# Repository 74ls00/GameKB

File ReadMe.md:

[Форум проекта](https://forum.geekboards.ru/viewtopic.php?t=13140)

------------------------------------------------------------------------------------

Easy AVR USB Keyboard Firmware Keymapper 
прошивка и графический конфигурфтор клавиш.

https://github.com/74ls00/GameKB_fw

Полная версия клавиатуры.

------------------------------------------------------------------------------------

tmk_keyboard \keyboard\korbord прошивка контролера 6KRO, готов только нумпад.

https://github.com/74ls00/GameKB_tmk

------------------------------------------------------------------------------------

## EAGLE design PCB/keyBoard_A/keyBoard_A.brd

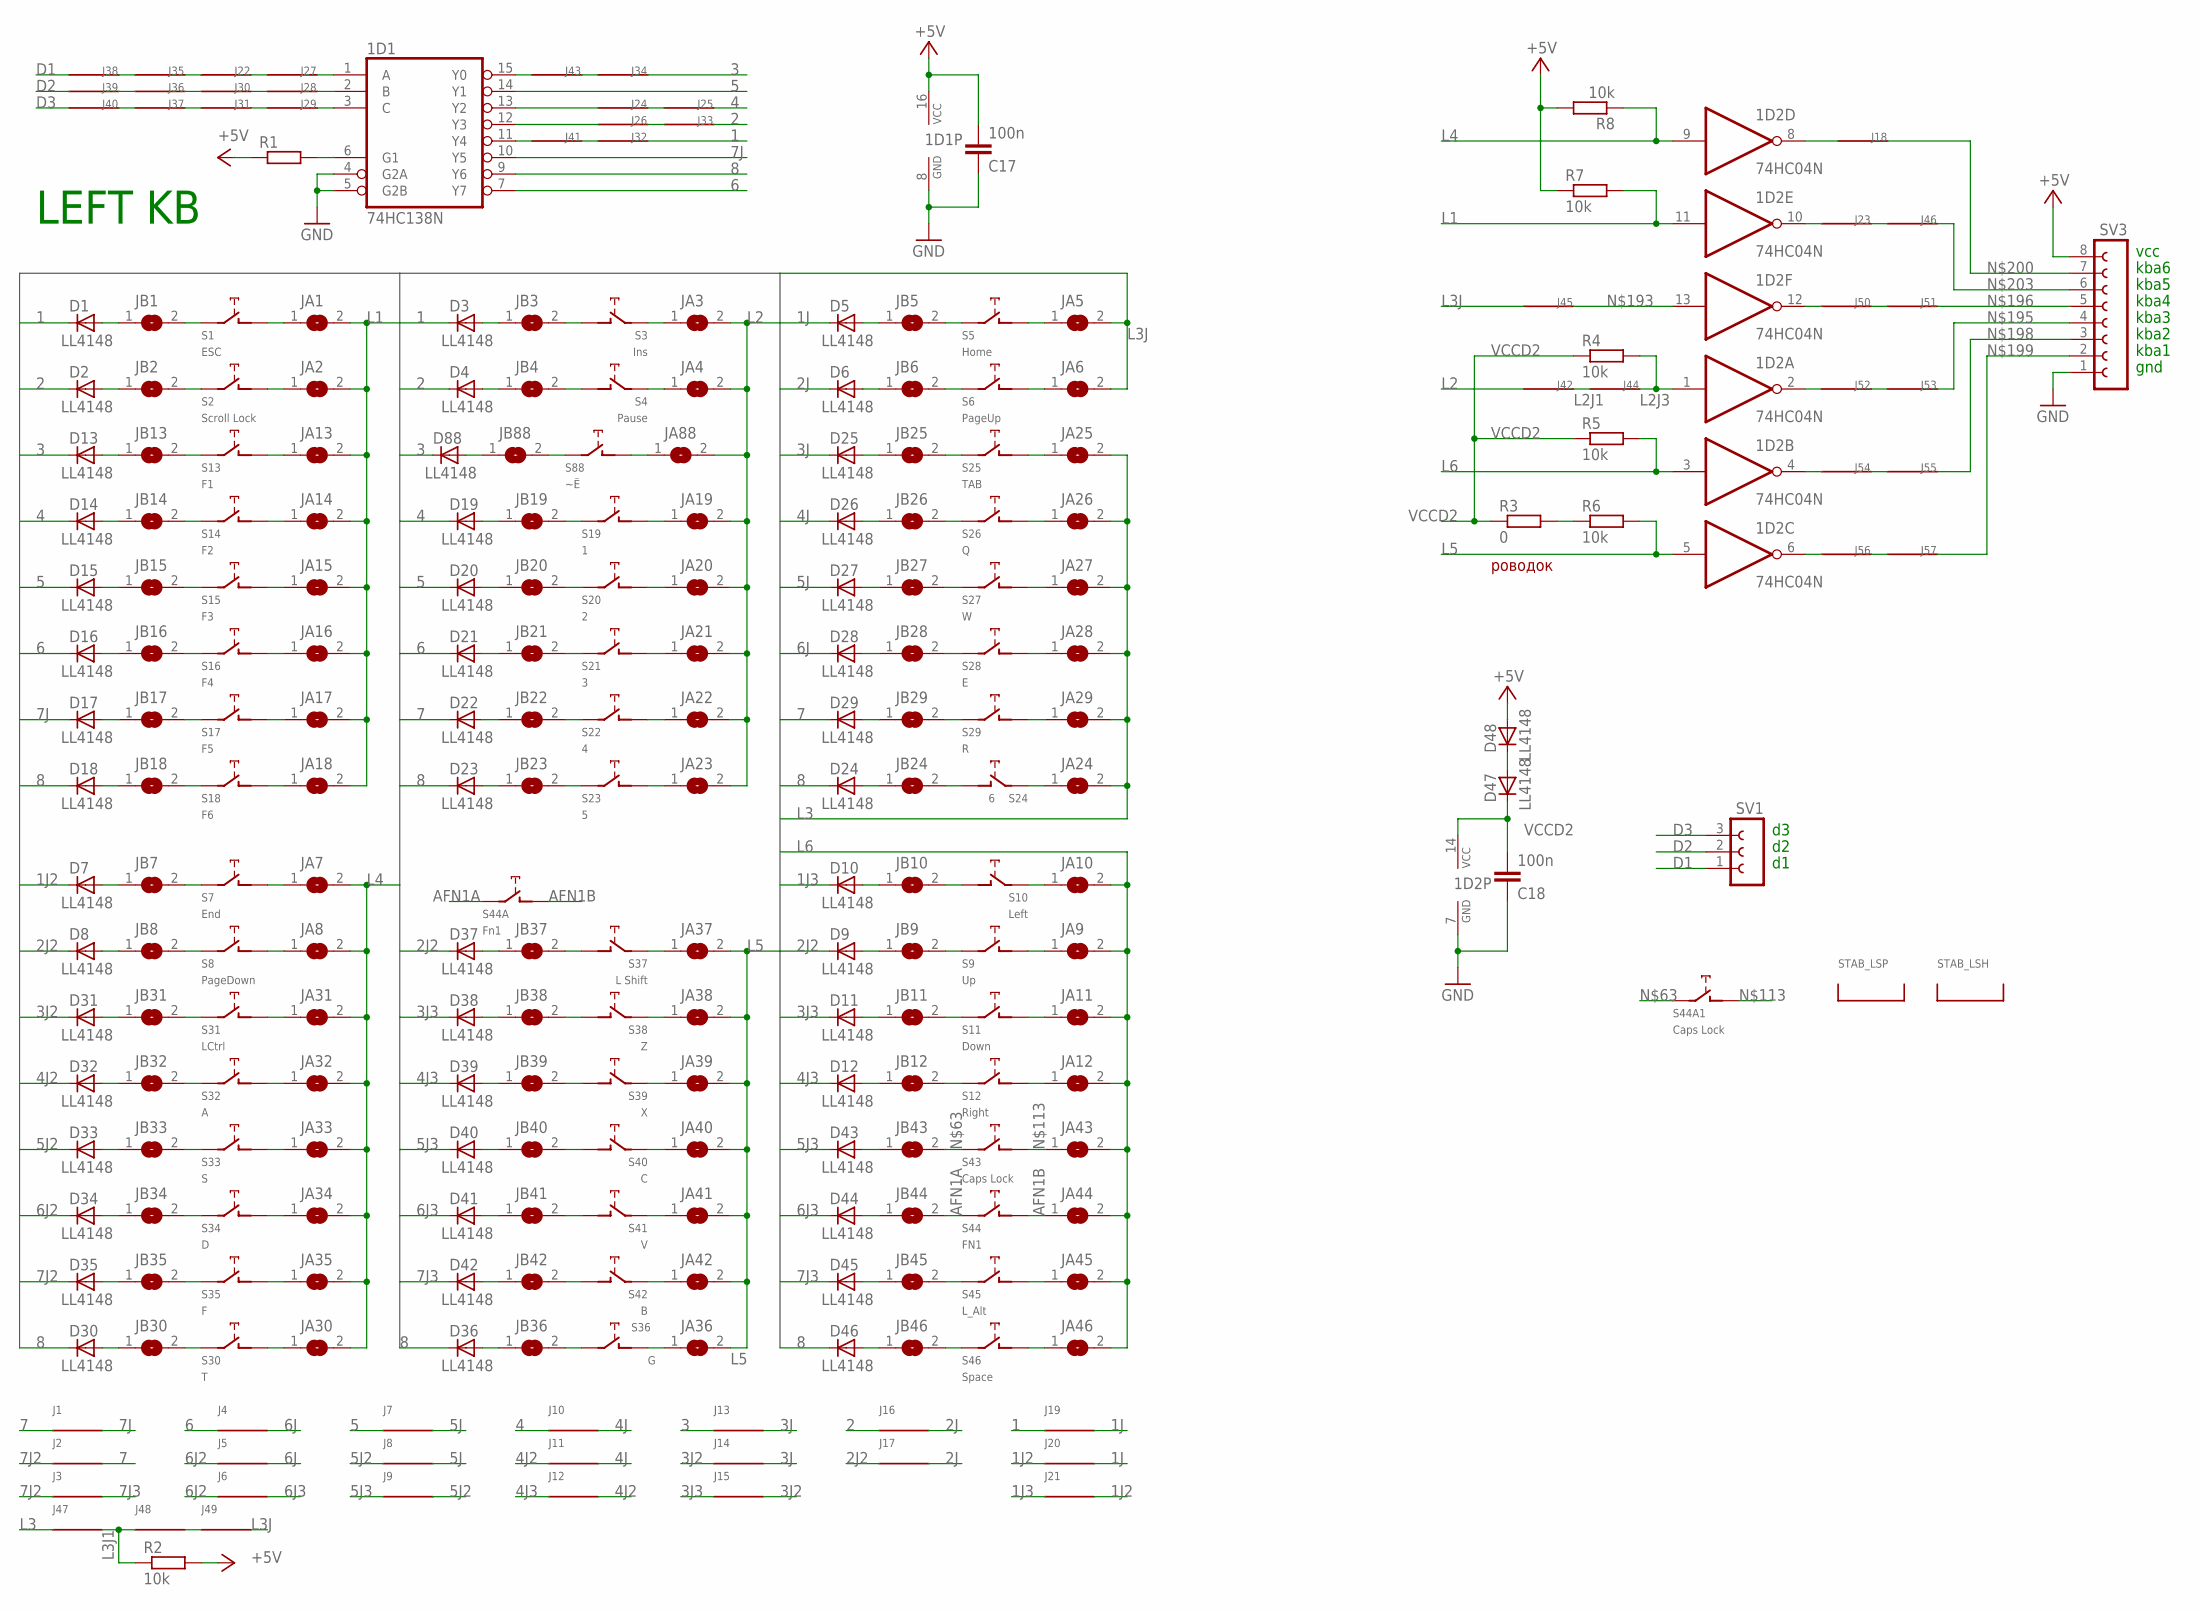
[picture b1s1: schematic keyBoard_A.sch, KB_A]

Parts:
1D1: 74HC138N; DIL16
1D2: 74HC04N; DIL14
C17, C18: 100n; C0805
D1, D2, D3, D4, D5, D6, D7, D8, D9, D10, D11, D12, D13, D14, D15, D16, D17, D18, D19, D20, D21, D22, D23, D24, D25, D26, D27, D28, D29, D30, D31, D32, D33, D34, D35, D36, D37, D38, D39, D40, D41, D42, D43, D44, D45, D46, D47, D48, D88: LL4148; SOD80C
J1, J2, J3, J4, J5, J6, J7, J8, J9, J10, J11, J12, J13, J14, J15, J16, J17, J18, J19, J20, J21, J22, J23, J24, J25, J26, J27, J28, J29, J30, J31, J32, J33, J34, J35, J36, J37, J38, J39, J40, J41, J42, J43, J44, J45, J46, J47, J48, J49, J50, J51, J52, J53, J54, J55, J56, J57: J; R1206W
JA1, JA2, JA3, JA4, JA5, JA6, JA7, JA8, JA9, JA10, JA11, JA12, JA13, JA14, JA15, JA16, JA17, JA18, JA19, JA20, JA21, JA22, JA23, JA24, JA25, JA26, JA27, JA28, JA29, JA30, JA31, JA32, JA33, JA34, JA35, JA36, JA37, JA38, JA39, JA40, JA41, JA42, JA43, JA44, JA45, JA46, JA88: SJ
JB1, JB3, JB4, JB6, JB7, JB8, JB9, JB10, JB11, JB12, JB13, JB16, JB17, JB18, JB19, JB20, JB21, JB22, JB23, JB24, JB25, JB26, JB27, JB28, JB29, JB30, JB31, JB32, JB33, JB34, JB35, JB36, JB37, JB38, JB39, JB40, JB41, JB42, JB43, JB44, JB45, JB46, JB88: SJ
JB2, JB5, JB14, JB15: SJ; SJ@1
R1: R-EU_R1206W; R1206W
R2, R5, R6, R7: 10k; R1206W
R3: 0; R1206W
R4, R8: 10k; R0805
S1: ESC; CHERRY-MX-4P
S2: Scroll Lock; CHERRY-MX-4P
S3: Ins; CHERRY-MX-4P
S4: Pause; CHERRY-MX-4P
S5: Home; CHERRY-MX-4P
S6: PageUp; CHERRY-MX-4P
S7: End; CHERRY-MX-4P
S8: PageDown; CHERRY-MX-4P
S9: Up; CHERRY-MX-4P
S10: Left; CHERRY-MX-4P
S11: Down; CHERRY-MX-4P
S12: Right; CHERRY-MX-4P
S13: F1; CHERRY-MX-4P
S14: F2; CHERRY-MX-4P
S15: F3; CHERRY-MX-4P
S16: F4; CHERRY-MX-4P
S17: F5; CHERRY-MX-4P
S18: F6; CHERRY-MX-4P
S19: 1; CHERRY-MX-4P
S20: 2; CHERRY-MX-4P
S21: 3; CHERRY-MX-4P
S22: 4; CHERRY-MX-4P
S23: 5; CHERRY-MX-4P
S24: 6; CHERRY-MX-4P
S25: TAB; CHERRY-MX-4P
S26: Q; CHERRY-MX-4P
S27: W; CHERRY-MX-4P
S28: E; CHERRY-MX-4P
S29: R; CHERRY-MX-4P
S30: T; CHERRY-MX-4P
S31: LCtrl; CHERRY-MX-4P
S32: A; CHERRY-MX-4P
S33: S; CHERRY-MX-4P
S34: D; CHERRY-MX-4P
S35: F; CHERRY-MX-4P
S36: G; CHERRY-MX-4P
S37: L Shift; CHERRY-MX-4P
S38: Z; CHERRY-MX-4P
S39: X; CHERRY-MX-4P
S40: C; CHERRY-MX-4P
S41: V; CHERRY-MX-4P
S42: B; CHERRY-MX-4P
S43: Caps Lock; CHERRY-MX-4P
S44: FN1; CHERRY-MX-4P
S44A: Fn1; CHERRY-MX
S44A1: Caps Lock; CHERRY-MX
S45: L_Alt; CHERRY-MX-4P
S46: Space; CHERRY-MX-4P
S88: ~Ё; CHERRY-MX-4P
STAB_LSH: STAB; ZEALIOS-PCB_2U
STAB_LSP: STAB; ZEALIOS-PCB_2U
SV1: FE03-1
SV3: FE08-1; FE08

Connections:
1: D1.C, D3.C, J19.2, J32.1
1J: D5.C, J19.1, J20.1
1J2: D7.C, J20.2, J21.1
1J3: D10.C, J21.2
2: D2.C, D4.C, J16.2, J33.1
2J: D6.C, J16.1, J17.1
2J2: D8.C, D9.C, D37.C, J17.2
3: D13.C, D88.C, J13.2, J34.1
3J: D25.C, J13.1, J14.1
3J2: D31.C, J14.2, J15.1
3J3: D11.C, D38.C, J15.2
4: D14.C, D19.C, J10.2, J25.1
4J: D26.C, J10.1, J11.1
4J2: D32.C, J11.2, J12.1
4J3: D12.C, D39.C, J12.2
5: 1D1.14 (Y1), D15.C, D20.C, J7.2
5J: D27.C, J7.1, J8.1
5J2: D33.C, J8.2, J9.1
5J3: D40.C, D43.C, J9.2
6: 1D1.7 (Y7), D16.C, D21.C, J4.2
6J: D28.C, J4.1, J5.1
6J2: D34.C, J5.2, J6.2
6J3: D41.C, D44.C, J6.1
7: D22.C, D29.C, J1.2, J2.1
7J: 1D1.10 (Y5), D17.C, J1.1
7J2: D35.C, J2.2, J3.2
7J3: D42.C, D45.C, J3.1
8: 1D1.9 (Y6), D18.C, D23.C, D24.C, D30.C, D36.C, D46.C
+5V: 1D1.16 (VCC), C17.2, D48.A, R1.1, R2.2, R7.1, R8.2, SV3.8
AFN1A: JB44.2, S44.SW1 (PIN-1), S44A.SW1 (PIN-1)
AFN1B: JA44.1, S44.SW2 (PIN-2), S44A.SW2 (PIN-2)
D1: J38.2, SV1.1
D2: J39.2, SV1.2
D3: J40.2, SV1.3
GND: 1D1.4 (G2A), 1D1.5 (G2B), 1D1.8 (GND), 1D2.7 (GND), C17.1, C18.1, SV3.1
L1: 1D2.11 (I), JA1.2, JA2.2, JA13.2, JA14.2, JA15.2, JA16.2, JA17.2, JA18.2, R7.2
L2: J42.2, JA3.2, JA4.2, JA19.2, JA20.2, JA21.2, JA22.2, JA23.2, JA88.2
L2J1: J42.1, J44.2
L2J3: 1D2.1 (I), J44.1, R4.2
L3: J47.2, JA24.2, JA25.2, JA26.2, JA27.2, JA28.2, JA29.2
L3J: J45.2, J49.1, JA5.2, JA6.2
L3J1: J47.1, J48.2, R2.1
L4: 1D2.9 (I), JA7.2, JA8.2, JA30.2, JA31.2, JA32.2, JA33.2, JA34.2, JA35.2, R8.1
L5: 1D2.5 (I), JA36.2, JA37.2, JA38.2, JA39.2, JA40.2, JA41.2, JA42.2, R6.2
L5O: 1D2.6 (O), J56.2
L6: 1D2.3 (I), JA9.2, JA10.2, JA11.2, JA12.2, JA43.2, JA44.2, JA45.2, JA46.2, R5.2
unnamed: D15.A, JB15.1
unnamed: JB4.2, S4.SW2 (PIN-2)
unnamed: D1.A, JB1.1
unnamed: JA4.1, S4.SW1 (PIN-1)
unnamed: JB14.2, S14.SW1 (PIN-1)
unnamed: JB20.2, S20.SW1 (PIN-1)
unnamed: JB32.2, S32.SW1 (PIN-1)
unnamed: JB38.2, S38.SW2 (PIN-2)
unnamed: JB6.2, S6.SW1 (PIN-1)
unnamed: JA6.1, S6.SW2 (PIN-2)
unnamed: JA8.1, S8.SW2 (PIN-2)
unnamed: JB8.2, S8.SW1 (PIN-1)
unnamed: JB10.2, S10.SW2 (PIN-2)
unnamed: JB1.2, S1.SW1 (PIN-1)
unnamed: D2.A, JB2.1
unnamed: JB2.2, S2.SW1 (PIN-1)
unnamed: JA2.1, S2.SW2 (PIN-2)
unnamed: D16.A, JB16.1
unnamed: JB3.2, S3.SW2 (PIN-2)
unnamed: JB5.2, S5.SW1 (PIN-1)
unnamed: JB7.2, S7.SW1 (PIN-1)
unnamed: JB9.2, S9.SW1 (PIN-1)
unnamed: JB11.2, S11.SW1 (PIN-1)
unnamed: D3.A, JB3.1
unnamed: JB12.2, S12.SW1 (PIN-1)
unnamed: D5.A, JB5.1
unnamed: D7.A, JB7.1
unnamed: JA10.1, S10.SW1 (PIN-1)
unnamed: JA1.1, S1.SW2 (PIN-2)
unnamed: D9.A, JB9.1
unnamed: D11.A, JB11.1
unnamed: JA3.1, S3.SW1 (PIN-1)
unnamed: JA5.1, S5.SW2 (PIN-2)
unnamed: JA7.1, S7.SW2 (PIN-2)
unnamed: JA9.1, S9.SW2 (PIN-2)
unnamed: JA11.1, S11.SW2 (PIN-2)
unnamed: JA12.1, S12.SW2 (PIN-2)
unnamed: JA14.1, S14.SW2 (PIN-2)
unnamed: JB13.2, S13.SW1 (PIN-1)
unnamed: JA13.1, S13.SW2 (PIN-2)
unnamed: D14.A, JB14.1
unnamed: JB42.2, S42.SW2 (PIN-2)
unnamed: JA42.1, S42.SW1 (PIN-1)
unnamed: JB27.2, S27.SW1 (PIN-1)
unnamed: JA27.1, S27.SW2 (PIN-2)
unnamed: JB17.2, S17.SW1 (PIN-1)
unnamed: JA17.1, S17.SW2 (PIN-2)
unnamed: D24.A, JB24.1
unnamed: JB24.2, S24.SW2 (PIN-2)
unnamed: JA24.1, S24.SW1 (PIN-1)
unnamed: J22.1, J27.2
unnamed: D4.A, JB4.1
unnamed: D6.A, JB6.1
unnamed: D8.A, JB8.1
unnamed: D10.A, JB10.1
unnamed: D12.A, JB12.1
unnamed: D13.A, JB13.1
unnamed: JB19.2, S19.SW1 (PIN-1)
unnamed: JB25.2, S25.SW1 (PIN-1)
unnamed: 1D2.8 (O), J18.2
unnamed: JB31.2, S31.SW1 (PIN-1)
unnamed: JB37.2, S37.SW2 (PIN-2)
unnamed: JB43.2, S43.SW1 (PIN-1), S44A1.SW1 (PIN-1)
unnamed: JB26.2, S26.SW1 (PIN-1)
unnamed: JB41.2, S41.SW2 (PIN-2)
unnamed: JB18.2, S18.SW1 (PIN-1)
unnamed: 1D1.13 (Y2), J24.2
unnamed: JB30.2, S30.SW1 (PIN-1)
unnamed: JB36.2, S36.SW1 (PIN-1)
unnamed: J24.1, J25.2
unnamed: JB23.2, S23.SW1 (PIN-1)
unnamed: JB29.2, S29.SW1 (PIN-1)
unnamed: JB35.2, S35.SW1 (PIN-1)
unnamed: JA41.1, S41.SW1 (PIN-1)
unnamed: JB16.2, S16.SW1 (PIN-1)
unnamed: JB22.2, S22.SW1 (PIN-1)
unnamed: JB28.2, S28.SW1 (PIN-1)
unnamed: JB34.2, S34.SW1 (PIN-1)
unnamed: JB40.2, S40.SW2 (PIN-2)
unnamed: JB46.2, S46.SW1 (PIN-1)
unnamed: JB15.2, S15.SW1 (PIN-1)
unnamed: JB21.2, S21.SW1 (PIN-1)
unnamed: JB33.2, S33.SW1 (PIN-1)
unnamed: JB39.2, S39.SW2 (PIN-2)
unnamed: JB45.2, S45.SW1 (PIN-1)
unnamed: JA15.1, S15.SW2 (PIN-2)
unnamed: JA18.1, S18.SW2 (PIN-2)
unnamed: JA20.1, S20.SW2 (PIN-2)
unnamed: JA22.1, S22.SW2 (PIN-2)
unnamed: JA23.1, S23.SW2 (PIN-2)
unnamed: JA25.1, S25.SW2 (PIN-2)
unnamed: JA26.1, S26.SW2 (PIN-2)
unnamed: JA28.1, S28.SW2 (PIN-2)
unnamed: JA29.1, S29.SW2 (PIN-2)
unnamed: JA30.1, S30.SW2 (PIN-2)
unnamed: JA31.1, S31.SW2 (PIN-2)
unnamed: JA32.1, S32.SW2 (PIN-2)
unnamed: JA33.1, S33.SW2 (PIN-2)
unnamed: JA34.1, S34.SW2 (PIN-2)
unnamed: JA35.1, S35.SW2 (PIN-2)
unnamed: JA36.1, S36.SW2 (PIN-2)
unnamed: JA38.1, S38.SW1 (PIN-1)
unnamed: JA39.1, S39.SW1 (PIN-1)
unnamed: JA40.1, S40.SW1 (PIN-1)
unnamed: JB88.2, S88.SW1 (PIN-1)
unnamed: JA43.1, S43.SW2 (PIN-2), S44A1.SW2 (PIN-2)
unnamed: JA45.1, S45.SW2 (PIN-2)
unnamed: JA46.1, S46.SW2 (PIN-2)
unnamed: JA19.1, S19.SW2 (PIN-2)
unnamed: JA88.1, S88.SW2 (PIN-2)
unnamed: JA21.1, S21.SW2 (PIN-2)
unnamed: JA16.1, S16.SW2 (PIN-2)
unnamed: D17.A, JB17.1
unnamed: D18.A, JB18.1
unnamed: D19.A, JB19.1
unnamed: D20.A, JB20.1
unnamed: D21.A, JB21.1
unnamed: D22.A, JB22.1
unnamed: D23.A, JB23.1
unnamed: D25.A, JB25.1
unnamed: D26.A, JB26.1
unnamed: D27.A, JB27.1
unnamed: D28.A, JB28.1
unnamed: D29.A, JB29.1
unnamed: D30.A, JB30.1
unnamed: D31.A, JB31.1
unnamed: D32.A, JB32.1
unnamed: D33.A, JB33.1
unnamed: D34.A, JB34.1
unnamed: D35.A, JB35.1
unnamed: D36.A, JB36.1
unnamed: D37.A, JB37.1
unnamed: D38.A, JB38.1
unnamed: D39.A, JB39.1
unnamed: D40.A, JB40.1
unnamed: D41.A, JB41.1
unnamed: D42.A, JB42.1
unnamed: D43.A, JB43.1
unnamed: D44.A, JB44.1
unnamed: D45.A, JB45.1
unnamed: D46.A, JB46.1
unnamed: D88.A, JB88.1
unnamed: 1D1.15 (Y0), J43.2
unnamed: 1D1.1 (A), J27.1
unnamed: 1D1.2 (B), J28.1
unnamed: 1D1.3 (C), J29.1
unnamed: J28.2, J30.1
unnamed: J29.2, J31.1
unnamed: J26.1, J33.2
unnamed: J35.2, J38.1
unnamed: J36.2, J39.1
unnamed: J37.2, J40.1
unnamed: J31.2, J37.1
unnamed: J30.2, J36.1
unnamed: J22.2, J35.1
unnamed: J32.2, J41.1
unnamed: 1D1.11 (Y4), J41.2
unnamed: 1D1.12 (Y3), J26.2
unnamed: J34.2, J43.1
unnamed: D47.A, D48.C
unnamed: 1D2.13 (I), J45.1
unnamed: J53.1, SV3.4
unnamed: J51.1, SV3.5
unnamed: 1D2.10 (O), J23.2
unnamed: J55.1, SV3.3
unnamed: J57.1, SV3.2
unnamed: J18.1, SV3.7
unnamed: J46.1, SV3.6
unnamed: J48.1, J49.2
unnamed: J23.1, J46.2
unnamed: 1D2.12 (O), J50.2
unnamed: J50.1, J51.2
unnamed: 1D2.2 (O), J52.2
unnamed: J52.1, J53.2
unnamed: 1D2.4 (O), J54.2
unnamed: JA37.1, S37.SW1 (PIN-1)
unnamed: J54.1, J55.2
unnamed: J56.1, J57.2
unnamed: R3.2, R6.1
unnamed: 1D1.6 (G1), R1.2
VCCD2: 1D2.14 (VCC), C18.2, D47.C, R3.1, R4.1, R5.1

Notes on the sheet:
vcc
gnd
LEFT KB
kba1
kba2
kba3
kba4
kba5
kba6
роводок

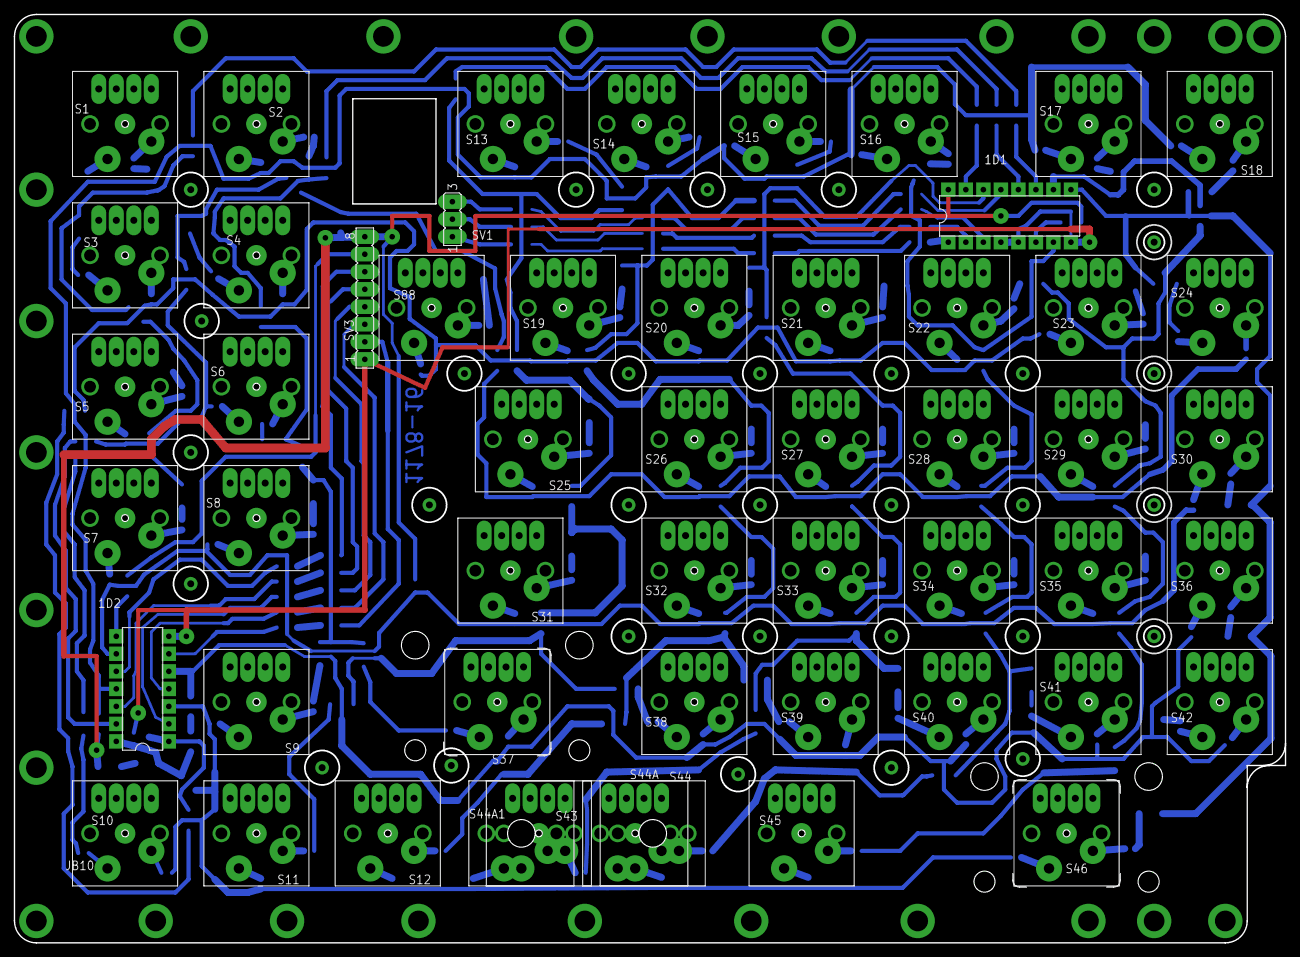
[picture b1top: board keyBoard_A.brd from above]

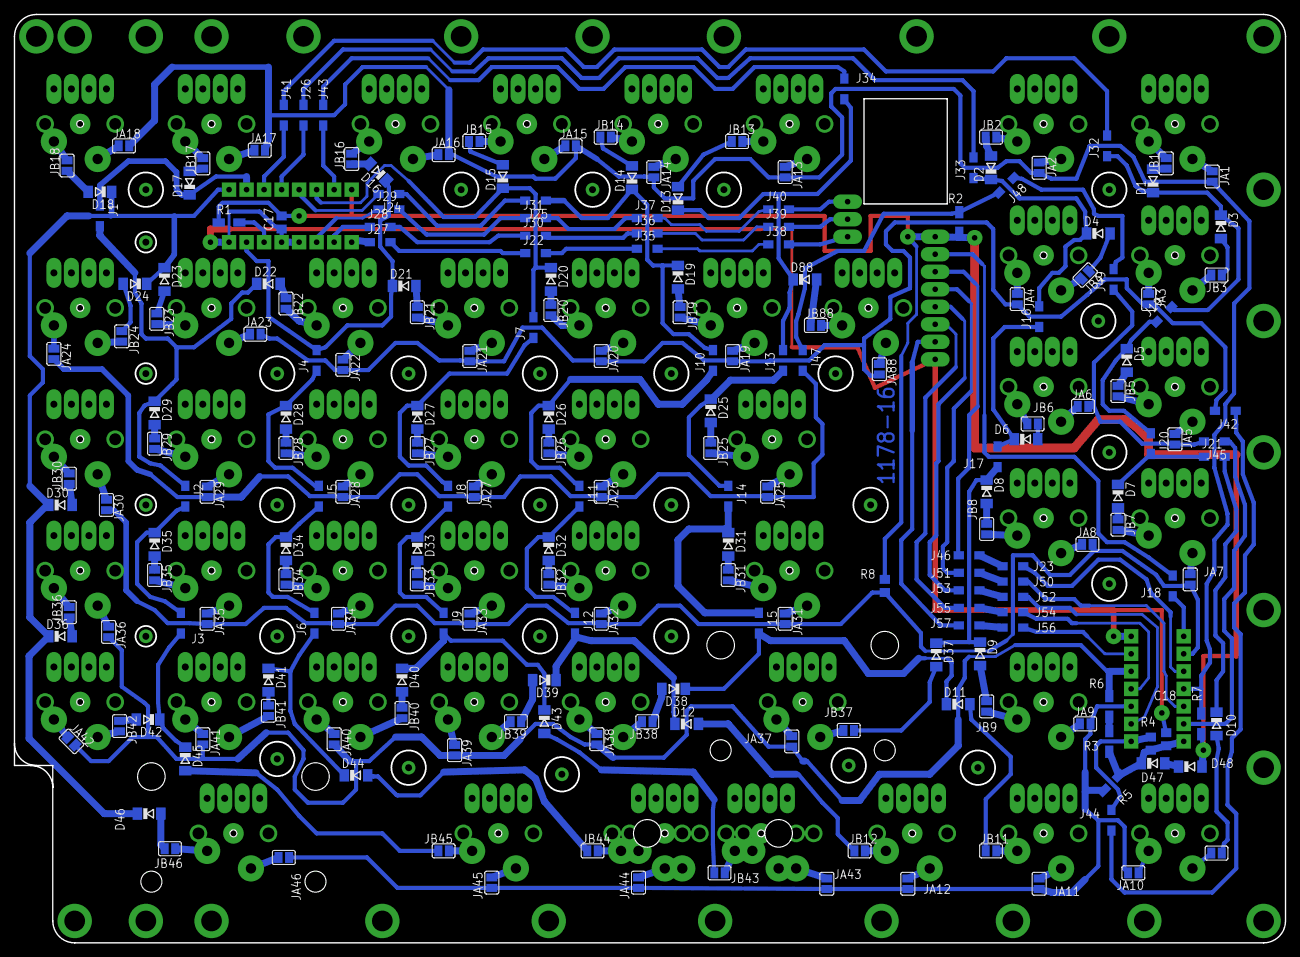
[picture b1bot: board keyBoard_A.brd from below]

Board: 2 copper layers, 184.3 x 134.6 mm, 321 parts (14 on the bottom side), 227 nets.

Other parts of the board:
U$1, U$2, U$3, U$4, U$5, U$6, U$7, U$8, U$9, U$10, U$11, U$12, U$13, U$14, U$18, U$19, U$20, U$21, U$23, U$24, U$25, U$26, U$27, U$29, U$30, U$31, U$32, U$33, U$35, U$36, U$37, U$38, U$39, U$40, U$41, U$42, U$43, U$44, U$45, U$46, U$49, U$52, U$82, U$88: 18X18
U$15, U$16, U$48, U$50, U$51, U$91: 18X23
U$17, U$47, U$53: 18X52
U$22: 18X37
U$28: 18X33
U$34: 18X28

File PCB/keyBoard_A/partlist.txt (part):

Partlist

Exported from keyBoard_A.brd at 2016-08-28 15:22:43

EAGLE Version 6.3.0 Copyright (c) 1988-2012 CadSoft

Assembly variant: 

Part     Value          Package      Library     Position (mil)        Orientation

1D1      74HC138N       DIL16        detali_main (6725 4350)           R0
1D2      74HC04N        DIL14        detali_main (1775 1650)           R90
C17      100n           C0805        rcl         (6775 4312.5)         MR90
C18      100n           C0805        rcl         (1725 1362.5)         MR270
D1       LL4148         SOD80C       detali      (1800 4550)           R270
D2       LL4148         SOD80C       detali      (2725 4625)           R270
D3       LL4148         SOD80C       detali      (1412.5 4287.5)       R90
D4       LL4148         SOD80C       detali      (2112.5 4250)         R0
D5       LL4148         SOD80C       detali      (1950 3525)           R90
D6       LL4148         SOD80C       detali      (2525 3075)           R0
D7       LL4148         SOD80C       detali      (2000 2750)           R90
D8       LL4148         SOD80C       detali      (2750 2775)           R90
D9       LL4148         SOD80C       detali      (2850 1850)           R90
D10      LL4148         SOD80C       detali      (1437.5 1462.5)       R90
D11      LL4148         SOD80C       detali      (2912.5 1562.5)       R0
D12      LL4148         SOD80C       detali      (4525 1375)           R0
D13      LL4148         SOD80C       detali      (4512.5 4450)         R270
D14      LL4148         SOD80C       detali      (4775 4568.625)       R270
D15      LL4148         SOD80C       detali      (5512.5 4575)         R270
D16      LL4148         SOD80C       detali      (6225 4600)           R225
D17      LL4148         SOD80C       detali      (7300 4537.5)         R270
D18      LL4148         SOD80C       detali      (7812.5 4487.5)       R180
D19      LL4148         SOD80C       detali      (4512.5 4000)         R90
D20      LL4148         SOD80C       detali      (5237.5 3987.5)       R90
D21      LL4148         SOD80C       detali      (6075 3950)           R0
D22      LL4148         SOD80C       detali      (6850 3962.5)         R0
D23      LL4148         SOD80C       detali      (7443.75 3987.5)      R90
D24      LL4148         SOD80C       detali      (7612.5 3962.5)       R180
D25      LL4148         SOD80C       detali      (4325 3237.5)         R90
D26      LL4148         SOD80C       detali      (5250 3200)           R90
D27      LL4148         SOD80C       detali      (6000 3200)           R90
D28      LL4148         SOD80C       detali      (6750 3200)           R90
D29      LL4148         SOD80C       detali      (7500 3225)           R90
D30      LL4148         SOD80C       detali      (8037.5 2700)         R0
D31      LL4148         SOD80C       detali      (4225 2475)           R90
D32      LL4148         SOD80C       detali      (5250 2450)           R90
D33      LL4148         SOD80C       detali      (6000 2450)           R90
D34      LL4148         SOD80C       detali      (6750 2450)           R90
D35      LL4148         SOD80C       detali      (7500 2475)           R90
D36      LL4148         SOD80C       detali      (8037.5 1950)         R0
D37      LL4148         SOD80C       detali      (3225 1943.75)        R90
D38      LL4148         SOD80C       detali      (4537.5 1650)         R180
D39      LL4148         SOD80C       detali      (5275 1700)           R180
D40      LL4148         SOD80C       detali      (6087.5 1700)         R90
D41      LL4148         SOD80C       detali      (6850 1700)           R90
D42      LL4148         SOD80C       detali      (7537.5 1475)         R180
D43      LL4148         SOD80C       detali      (5275 1462.5)         R90
D44      LL4148         SOD80C       detali      (6568.75 1250)        R90
D45      LL4148         SOD80C       detali      (7325 1250)           R90
D46      LL4148         SOD80C       detali      (7362.5 906.25)       R90
D47      LL4148         SOD80C       detali      (1800 1225)           R0
D48      LL4148         SOD80C       detali      (1587.5 1206.25)      R0
D88      LL4148         SOD80C       detali      (3787.5 3987.5)       R0
J1       J              R1206W       detali_main (7812.5 4350)         R90
J2       J              R1206W       detali_main (7325 2750)           R90
J3       J              R1206W       detali_main (7350 2025)           R270
J4       J              R1206W       detali_main (6575 3525)           R270
J5       J              R1206W       detali_main (6562.5 2750)         R90
J6       J              R1206W       detali_main (6587.5 2025)         R270
J7       J              R1206W       detali_main (5337.5 3712.5)       R270
J8       J              R1206W       detali_main (5825 2750)           R90
J9       J              R1206W       detali_main (5850 2025)           R90
J10      J              R1206W       detali_main (4312.5 3525)         R270
J11      J              R1206W       detali_main (5075 2750)           R90
J12      J              R1206W       detali_main (5100 2025)           R90
J13      J              R1206W       detali_main (3912.5 3525)         R270
J14      J              R1206W       detali_main (4225 2750)           R90
J15      J              R1206W       detali_main (4250 2025)           R90
J16      J              R1206W       detali_main (2450 3775)           R270
J17      J              R1206W       detali_main (2687.5 2975)         R90
J18      J              R1206W       detali_main (1687.5 2237.5)       R90
J19      J              R1206W       detali_main (1737.5 3787.5)       R315
J20      J              R1206W       detali_main (1812.5 3050)         R90
J21      J              R1206W       detali_main (1450 2975)           R0
J22      J              R1206W       detali_main (5325 4137.5)         R0
J23      J              R1206W       detali_main (2600 2350)           R0
J24      J              R1206W       detali_main (6162.5 4475)         R180
J25      J              R1206W       detali_main (5325 4437.5)         R180
J26      J              R1206W       detali_main (6650 4925)           R90
J27      J              R1206W       detali_main (6212.5 4200)         R0
J28      J              R1206W       detali_main (6212.5 4287.5)       R0
J29      J              R1206W       detali_main (6162.5 4387.5)       R0
J30      J              R1206W       detali_main (5325 4237.5)         R0
J31      J              R1206W       detali_main (5325 4337.5)         R0
J32      J              R1206W       detali_main (2062.5 4750)         R270
J33      J              R1206W       detali_main (2825 4625)           R270
J34      J              R1206W       detali_main (3487.5 5075)         R270
J35      J              R1206W       detali_main (4687.5 4162.5)       R0
J36      J              R1206W       detali_main (4687.5 4250)         R0
J37      J              R1206W       detali_main (4687.5 4337.5)       R0
J38      J              R1206W       detali_main (3937.5 4187.5)       R0
J39      J              R1206W       detali_main (3937.5 4287.5)       R0
J40      J              R1206W       detali_main (3937.5 4387.5)       R0
J41      J              R1206W       detali_main (6762.5 4925)         R90
J42      J              R1206W       detali_main (1387.5 3237.5)       R180
J43      J              R1206W       detali_main (6537.5 4925)         R90
J44      J              R1206W       detali_main (2037.5 900)          R90
J45      J              R1206W       detali_main (1450 3062.5)         R180
J46      J              R1206W       detali_main (2850 2412.5)         R0
J47      J              R1206W       detali_main (3800 3525)           R90
J48      J              R1206W       detali_main (2637.5 4525)         R135
J49      J              R1206W       detali_main (2025 3987.5)         R270
J50      J              R1206W       detali_main (2600 2262.5)         R0
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

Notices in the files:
firmware/EasyAVR/keymapper/easykeymap/boards/_korbord.py:
Copyright (C) 2013-2016 David Howland
This program is free software; you can redistribute it and/or modify
it under the terms of the GNU General Public License as published by
the Free Software Foundation; either version 2 of the License, or
(at your option) any later version.
parts and their libraries:
SparkFun-DigitalIC: Licensing: Creative Commons ShareAlike 4.0 International - https://creativecommons.org/licenses/by-sa/4.0
